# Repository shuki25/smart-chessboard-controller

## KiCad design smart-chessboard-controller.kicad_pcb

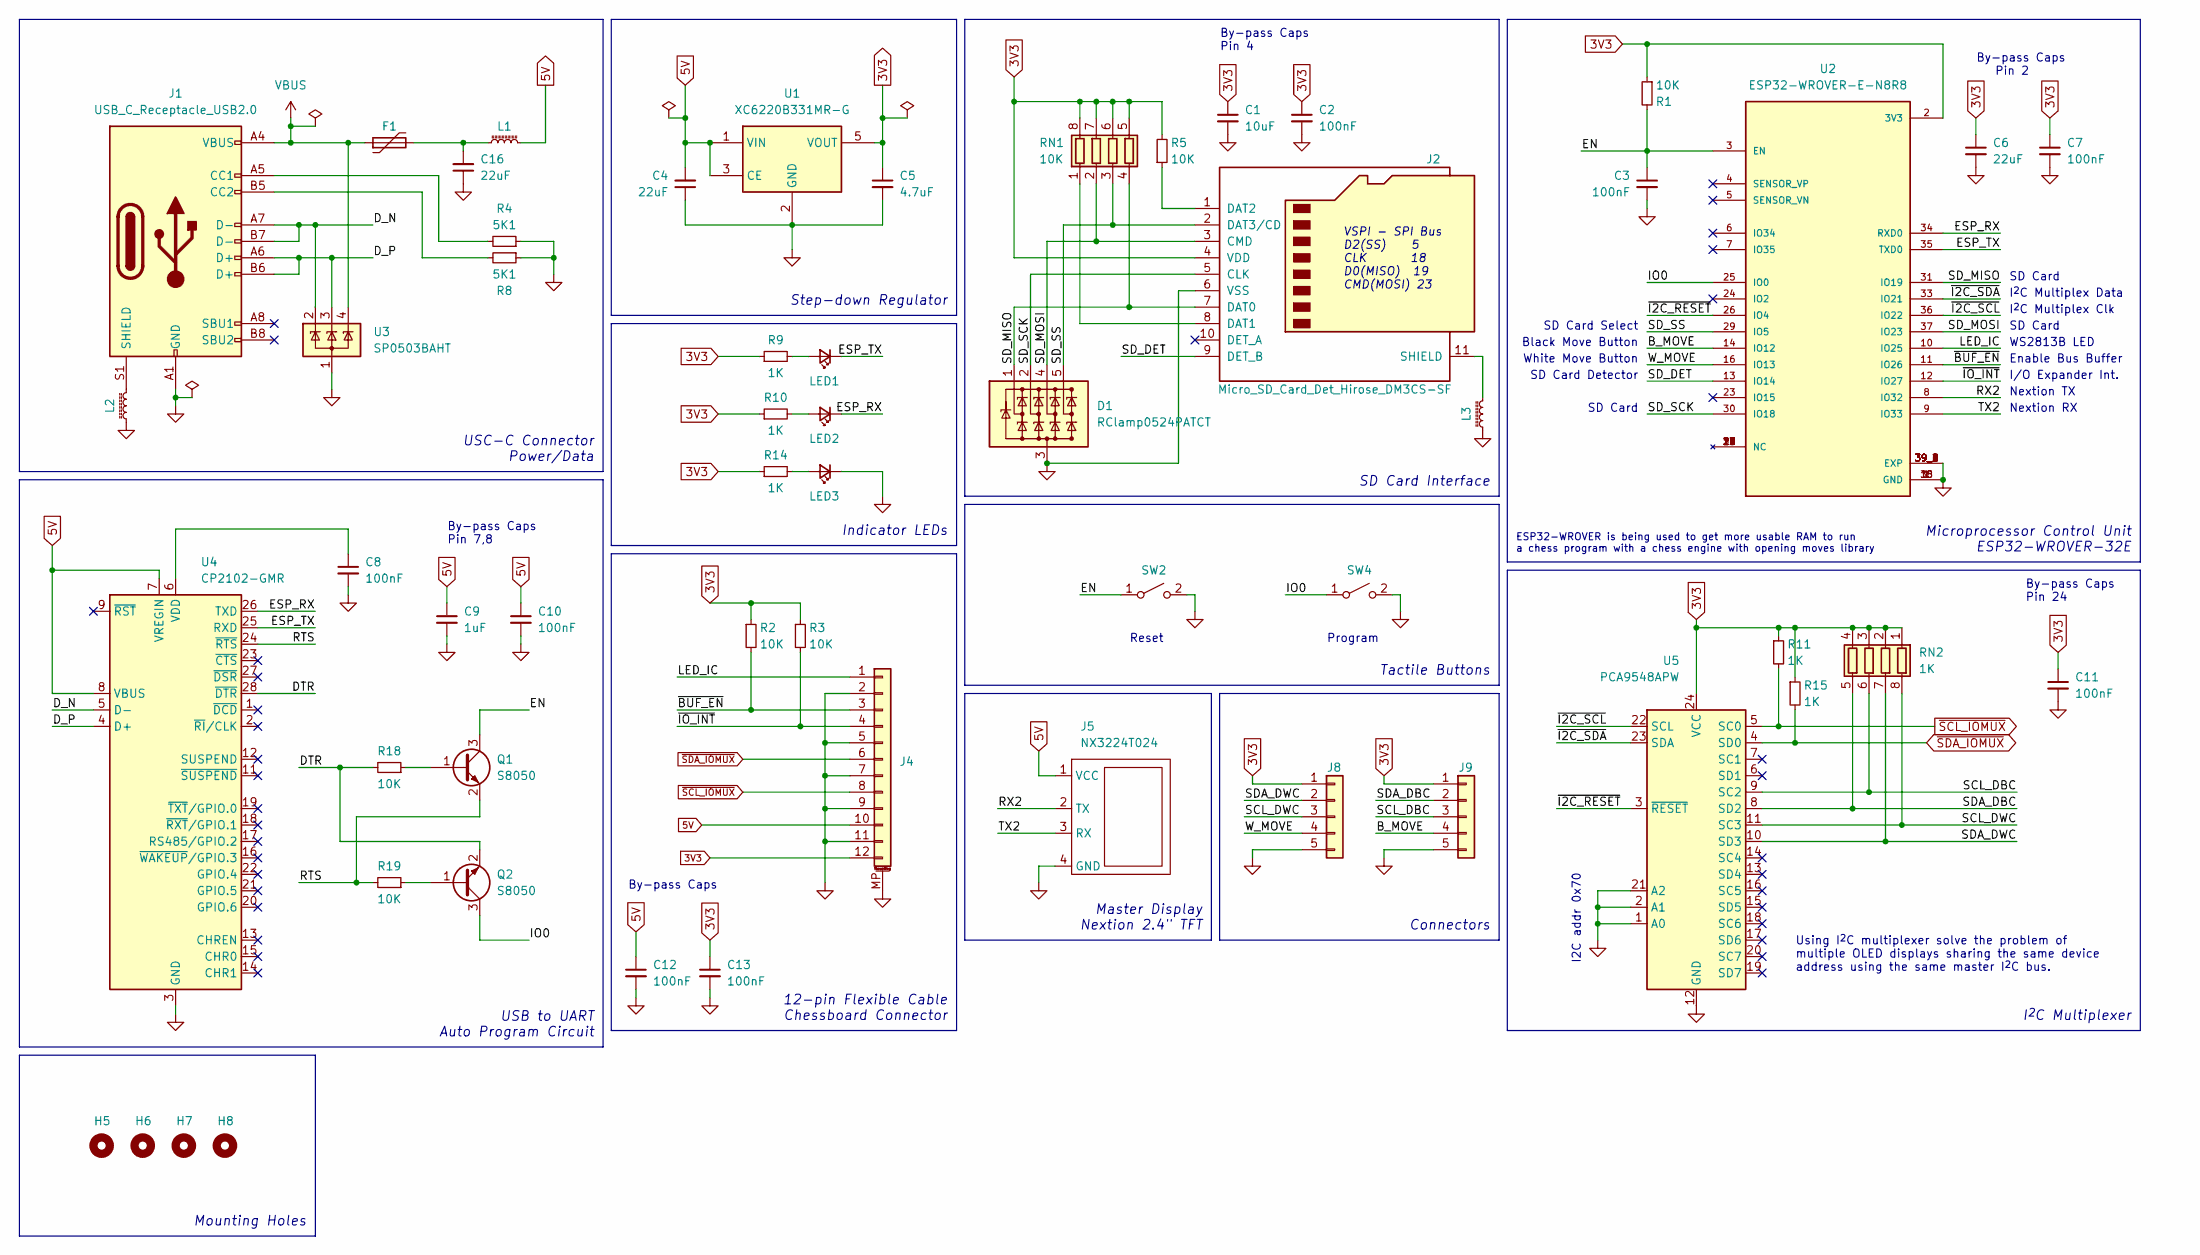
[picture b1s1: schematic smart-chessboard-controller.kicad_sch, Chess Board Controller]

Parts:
C1: 10uF; C_0603_1608Metric; LCSC C19702
C2, C3, C7, C8, C10, C11, C12, C13: 100nF; C_0603_1608Metric; LCSC C14663
C4, C6, C16: 22uF; C_0603_1608Metric; LCSC C59461
C5: 4.7uF; C_0603_1608Metric; LCSC C19666
C9: 1uF; C_0603_1608Metric; LCSC C14663
D1: RClamp0524PATCT; SLP2510P8; LCSC C40960
F1: BHFUSE BSMD1206-200-12V; Fuse_1206_3216Metric; LCSC C883135
H5, H6, H7, H8: MountingHole; MountingHole_2.7mm_M2.5_DIN965_Pad_TopBottom
J1: USB_C_Receptacle_USB2.0; USB_C_Receptable_918-418K2023S40001; LCSC C2982555
J2: Micro_SD_Card_Det_Hirose_DM3CS-SF; DM3CS-SF; LCSC C202111
J4: Conn_01x12_MountingPin; TE_1-84953-2_1x12-1MP_P1.0mm_Horizontal; LCSC C262718
J5: NX3224T024; JST_PH_S4B-PH-K_1x04_P2.00mm_Horizontal; LCSC C157926
J8, J9: Conn_01x05; JST_PH_S5B-PH-K_1x05_P2.00mm_Horizontal; LCSC C157923
L1, L2, L3: L_Ferrite_Small; L_0603_1608Metric; LCSC C62708
LED1: BLUE; LED_0603_1608Metric; LCSC C72041
LED2: GREEN; LED_0603_1608Metric; LCSC C72043
LED3: RED; LED_0603_1608Metric; LCSC C2286
Q1, Q2: S8050; SOT-23; LCSC C2146
R1, R2, R3, R5, R18, R19: 10K; R_0603_1608Metric; LCSC C25804
R4, R8: 5K1; R_0805_2012Metric; LCSC C27834
R9, R10, R11, R15: 1K; R_0603_1608Metric; LCSC C21190
R14: 1K; R_0603_1608Metric; MFR_PART_NBR 0805W8F4700T5E; LCSC C21190
RN1: 10K; R_Array_Convex_4x0603; LCSC C29718
RN2: 1K; R_Array_Convex_4x0603; LCSC C20197
SW2, SW4: SW_SPST; XKB-Connectivity-TS-1187A-B-A-B; LCSC C318884
U1: XC6220B331MR-G; SOT-23-5; LCSC C86534
U2: ESP32-WROVER-E-N8R8; XCVR_ESP32-WROVER-E-N4R8; PARTREV 1.6; LCSC C701348
U3: SP0503BAHT; SOT-143-4; LCSC C7074
U4: CP2102-GMR; QFN-28-1EP_5x5mm_P0.5mm_EP3.35x3.35mm; LCSC C6568
U5: PCA9548APW; TSSOP-24_4.4x7.8mm_P0.65mm; LCSC C21198

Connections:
3V3: C1.1, C2.1, C5.1, C6.1, C7.1, C11.1, C13.1, J2.4 (VDD), J4.12, J8.1, J9.1, R1.1, R2.1, R3.1, R5.2, R9.1, R10.1, R11.1, R14.1, R15.1, RN1.5 (R4.2), RN1.6 (R3.2), RN1.7 (R2.2), RN1.8 (R1.2), RN2.1 (R1.1), RN2.2 (R2.1), RN2.3 (R3.1), RN2.4 (R4.1), U1.5 (VOUT), U2.2 (3V3), U5.24 (VCC)
5V: C4.2, C9.1, C10.1, C12.1, J4.10, J5.1 (VCC), L1.2, U1.1 (VIN), U1.3 (CE), U4.7 (VREGIN), U4.8 (VBUS)
/B_MOVE: J9.4, U2.14 (IO12)
/DTR: Q2.2 (E), R18.2, U4.28 (~DTR)
/D_N: J1.A7 (D-), J1.B7 (D-), U3.2 (K), U4.5 (D-)
/D_P: J1.A6 (D+), J1.B6 (D+), U3.3 (K), U4.4 (D+)
/EN: C3.1, Q1.3 (C), R1.2, SW2.1 (A), U2.3 (EN)
/ESP_RX: LED2.1 (K), U2.34 (RXD0), U4.26 (TXD)
/ESP_TX: LED1.1 (K), U2.35 (TXD0), U4.25 (RXD)
/IO0: Q2.3 (C), SW4.1 (A), U2.25 (IO0)
/LED_IC: J4.1, U2.10 (IO25)
/RTS: Q1.2 (E), R19.2, U4.24 (~RTS)
/RX2: J5.2 (TX), U2.8 (IO32)
/SCL_DBC: J9.3, RN2.6 (R3.2), U5.9 (SC2)
/SCL_DWC: J8.3, RN2.8 (R1.2), U5.11 (SC3)
/SDA_DBC: J9.2, RN2.5 (R4.2), U5.8 (SD2)
/SDA_DWC: J8.2, RN2.7 (R2.2), U5.10 (SD3)
/SD_DET: J2.9 (DET_B), U2.13 (IO14)
/SD_MISO: D1.1 (K1), J2.7 (DAT0), RN1.4 (R4.1), U2.31 (IO19)
/SD_MOSI: D1.4 (K3), J2.3 (CMD), RN1.2 (R2.1), U2.37 (IO23)
/SD_SCK: D1.2 (K2), J2.5 (CLK), U2.30 (IO18)
/SD_SS: D1.5 (K4), J2.2 (DAT3/CD), RN1.3 (R3.1), U2.29 (IO5)
/TX2: J5.3 (RX), U2.9 (IO33)
/W_MOVE: J8.4, U2.16 (IO13)
/~BUF_EN: J4.3, R2.2, U2.11 (IO26)
/~I2C_RESET: U2.26 (IO4), U5.3 (~RESET)
/~I2C_SCL: U2.36 (IO22), U5.22 (SCL)
/~I2C_SDA: U2.33 (IO21), U5.23 (SDA)
/~IO_INT: J4.4, R3.2, U2.12 (IO27)
GND: C1.2, C2.2, C3.2, C4.1, C5.2, C6.2, C7.2, C8.2, C9.2, C10.2, C11.2, C12.2, C13.2, C16.1, D1.3 (A), J1.A1 (GND), J1.A12 (GND), J1.B1 (GND), J1.B12 (GND), J2.6 (VSS), J4.2, J4.5, J4.7, J4.9, J4.11, J4.MP (MountPin), J5.4 (GND), J8.5, J9.5, L2.1, L3.1, LED3.1 (K), R4.1, R8.1, SW2.2 (B), SW4.2 (B), U1.2 (GND), U2.1 (GND), U2.15 (GND), U2.38 (GND), U2.39_1 (EXP), U2.39_2 (EXP), U2.39_3 (EXP), U2.39_4 (EXP), U2.39_5 (EXP), U2.39_6 (EXP), U2.39_7 (EXP), U2.39_8 (EXP), U2.39_9 (EXP), U3.1 (A), U4.3 (GND), U4.29 (GND), U5.1 (A0), U5.2 (A1), U5.12 (GND), U5.21 (A2)
unnamed: C8.1, U4.6 (VDD)
unnamed: C16.2, F1.2, L1.1
unnamed: J1.A5 (CC1), R4.2
unnamed: J1.B5 (CC2), R8.2
unnamed: J1.S1 (SHIELD), J1.S2 (SHIELD), J1.S3 (SHIELD), J1.S4 (SHIELD), L2.2
unnamed: J2.1 (DAT2), R5.1
unnamed: J2.8 (DAT1), RN1.1 (R1.1)
unnamed: J2.11 (SHIELD), L3.2
unnamed: LED1.2 (A), R9.2
unnamed: LED2.2 (A), R10.2
unnamed: LED3.2 (A), R14.2
unnamed: Q1.1 (B), R18.1
unnamed: Q2.1 (B), R19.1
VBUS: F1.1, J1.A4 (VBUS), J1.A9 (VBUS), J1.B4 (VBUS), J1.B9 (VBUS), U3.4 (K)
~SCL_IOMUX: J4.8, R11.2, U5.5 (SC0)
~SDA_IOMUX: J4.6, R15.2, U5.4 (SD0)

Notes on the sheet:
SD Card
USB to UART Auto Program Circuit
I^{2}C Multiplex Clk
SD Card Detector
Master Display Nextion 2.4" TFT
By-pass Caps Pin 4
Reset
12-pin Flexible Cable Chessboard Connector
Nextion RX
Microprocessor Control Unit ESP32-WROVER-32E
USC-C Connector Power/Data
SD Card Interface
ESP32-WROVER is being used to get more usable RAM to run a chess program with a chess engine with opening moves library
Black Move Button
I^{2}C Multiplex Data
White Move Button
I^{2}C Multiplexer
WS2813B LED
Program
By-pass Caps Pin 24
By-pass Caps Pin 7,8
By-pass Caps
By-pass Caps Pin 2
Enable Bus Buffer
I2C addr 0x70
VSPI - SPI Bus D2(SS) 5 CLK 18 D0(MISO) 19 CMD(MOSI) 23
Step-down Regulator
Connectors
Using I^{2}C multiplexer solve the problem of multiple OLED displays sharing the same device address using the same master I^{2}C bus.
Nextion TX
Mounting Holes
Indicator LEDs
Tactile Buttons
SD Card Select
I/O Expander Int.

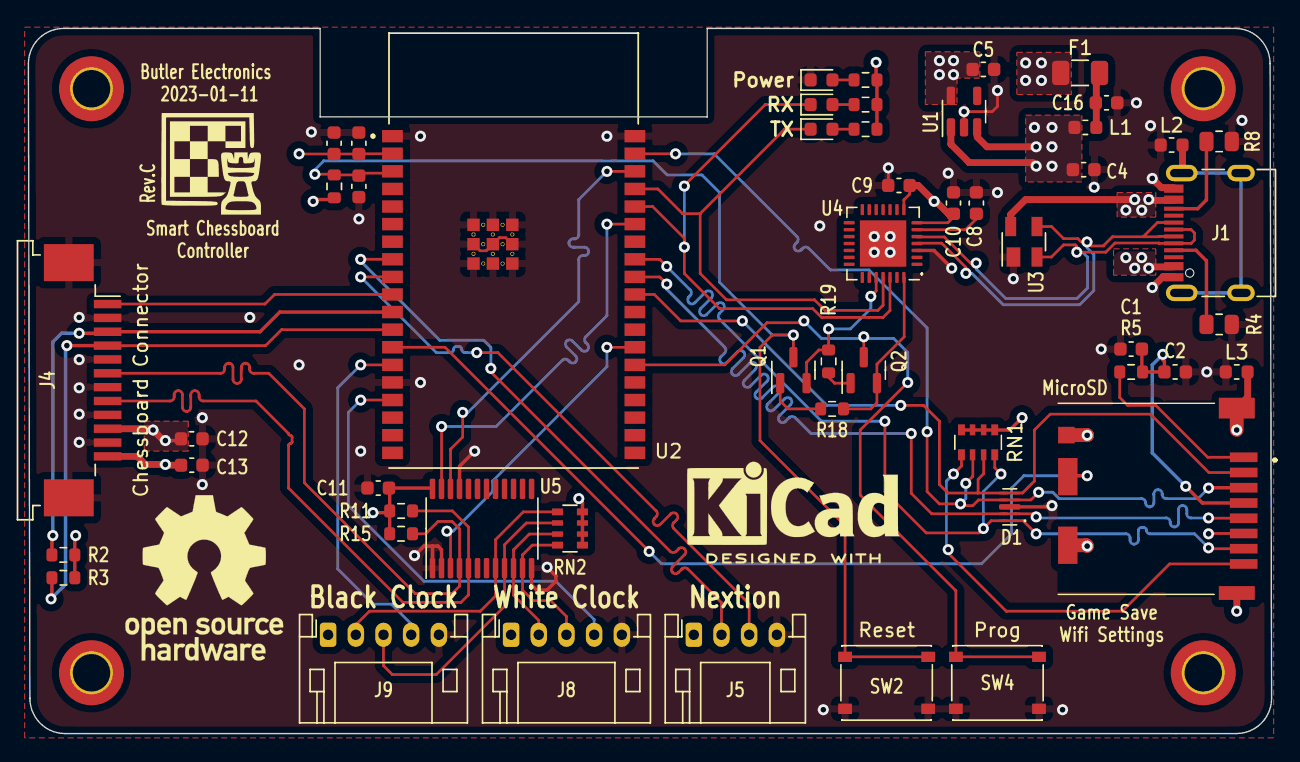
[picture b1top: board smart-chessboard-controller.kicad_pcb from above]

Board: 4 copper layers, 89.8 x 50.9 mm, 56 parts (0 on the bottom side), 46 nets.

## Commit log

2022-11-18 update layout
2022-11-18 move around pins on ESP32 to optimize PCB layout
2022-11-18 change mounting hole size
2022-11-18 add some traces
2022-11-21 add all traces and power traces
2022-11-21 add logos and fix DRC issues
2022-11-21 refactor LDO layout
2022-11-21 update labels
2022-11-25 move usb-c to the side of the pcb
    - revise ground nets for clock boards
    - add backup led IC data line if the voltage regulator fails
2022-11-25 update manufacturing files
2022-11-25 tune i2c trace length
2022-12-08 update production files
2022-12-08 update USB-C footprint to through hole
2022-12-11 fix pin assignment for black clock connector
2022-12-11 add 3d models for fusion 360
2022-12-12 remove chess clock/button
    Remove chess clock/buttons from controller design. They were
    moved to separate design since it's more expensive to
    manufacture boards with panelization. They charge extra if
    there are different designs with one gerber file with
    panelization.
2022-12-12 update 3d models
2022-12-24 fix issues from rev.B
2022-12-27 change pin assignment for io_int
2022-12-27 update schematic pdf
2022-12-27 add bypass caps
2022-12-28 update design to use ESP32 WROVER module
2023-01-05 add pad clearance for paste mask
2023-01-11 refactor schematic/pcb to add/remove components
    - remove ESP programmer Tag Connect interface
    - replace set of resistors to resistor array for SD card
    - add pull-up resistors for interrupt and bus buffer enable pin
    - tune trace length matching for data lines (i2c, ttl and spi)
2023-01-11 update SD card detect pin assignment
2023-01-12 replace USB-C part that was out of stock
2023-02-28 update settings
2023-03-12 update to kicad7 file format
